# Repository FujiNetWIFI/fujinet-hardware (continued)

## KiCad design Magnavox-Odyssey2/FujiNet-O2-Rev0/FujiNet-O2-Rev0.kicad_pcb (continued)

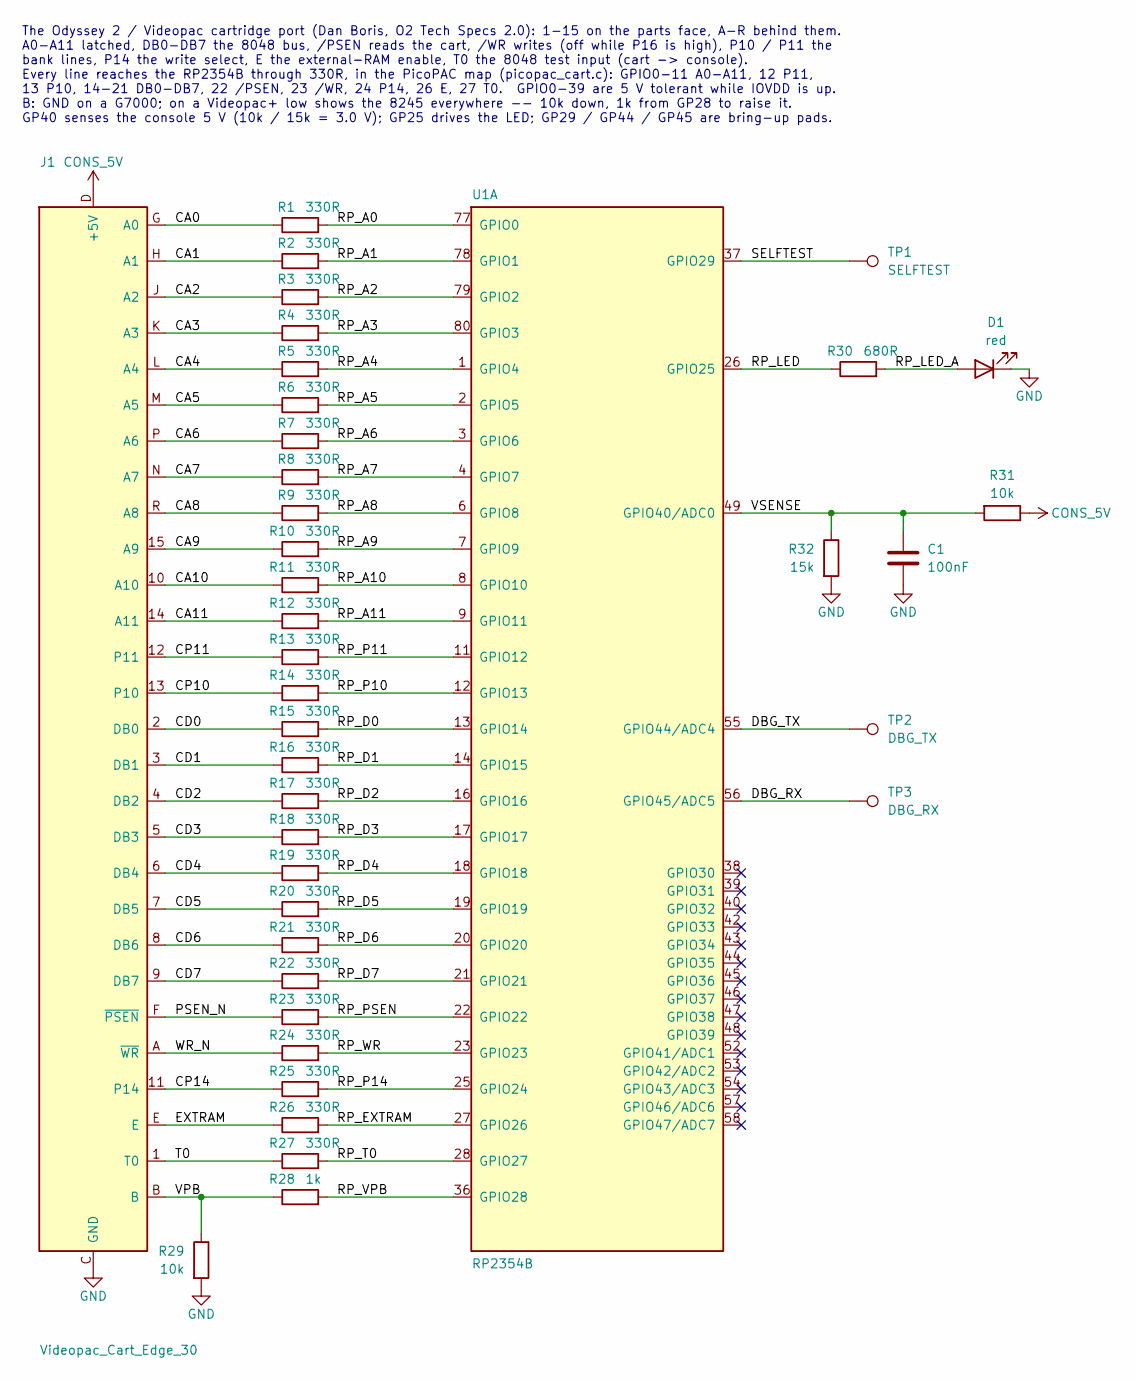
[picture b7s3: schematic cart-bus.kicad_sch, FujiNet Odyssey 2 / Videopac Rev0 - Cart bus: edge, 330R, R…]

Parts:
C1: 100nF; C_0603_1608Metric; MPN CC0603KRX7R9BB104; LCSC C14663
D1: red; LED_0603_1608Metric; MPN KT-0603R; LCSC C2286
J1: Videopac_Cart_Edge_30
R1, R2, R3, R4, R5, R6, R7, R8, R9, R10, R11, R12, R13, R14, R15, R16, R17, R18, R19, R20, R21, R22, R23, R24, R25, R26, R27: 330R; R_0603_1608Metric; MPN 0603WAF3300T5E; LCSC C23138
R28: 1k; R_0603_1608Metric; MPN 0603WAF1001T5E; LCSC C21190
R29, R31: 10k; R_0603_1608Metric; MPN 0603WAF1002T5E; LCSC C25804
R30: 680R; R_0603_1608Metric; MPN 0603WAF6800T5E; LCSC C23228
R32: 15k; R_0603_1608Metric; MPN 0603WAF1502T5E; LCSC C22809
TP1: SELFTEST; TestPoint_Pad_D1.5mm
TP2: DBG_TX; TestPoint_Pad_D1.5mm
TP3: DBG_RX; TestPoint_Pad_D1.5mm
U1: RP2354B; QFN-80-1EP_10x10mm_P0.4mm_EP3.4x3.4mm; MPN RP2354B; LCSC C39843328

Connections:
/cart-bus/CA0: J1.G (A0), R1.1
/cart-bus/CA1: J1.H (A1), R2.1
/cart-bus/CA2: J1.J (A2), R3.1
/cart-bus/CA3: J1.K (A3), R4.1
/cart-bus/CA4: J1.L (A4), R5.1
/cart-bus/CA5: J1.M (A5), R6.1
/cart-bus/CA6: J1.P (A6), R7.1
/cart-bus/CA7: J1.N (A7), R8.1
/cart-bus/CA8: J1.R (A8), R9.1
/cart-bus/CA9: J1.15 (A9), R10.1
/cart-bus/CA10: J1.10 (A10), R11.1
/cart-bus/CA11: J1.14 (A11), R12.1
/cart-bus/CD0: J1.2 (DB0), R15.1
/cart-bus/CD1: J1.3 (DB1), R16.1
/cart-bus/CD2: J1.4 (DB2), R17.1
/cart-bus/CD3: J1.5 (DB3), R18.1
/cart-bus/CD4: J1.6 (DB4), R19.1
/cart-bus/CD5: J1.7 (DB5), R20.1
/cart-bus/CD6: J1.8 (DB6), R21.1
/cart-bus/CD7: J1.9 (DB7), R22.1
/cart-bus/CP10: J1.13 (P10), R14.1
/cart-bus/CP11: J1.12 (P11), R13.1
/cart-bus/CP14: J1.11 (P14), R25.1
/cart-bus/DBG_RX: TP3.1, U1.56 (GPIO45/ADC5)
/cart-bus/DBG_TX: TP2.1, U1.55 (GPIO44/ADC4)
/cart-bus/EXTRAM: J1.E, R26.1
/cart-bus/PSEN_N: J1.F (~PSEN), R23.1
/cart-bus/RP_A0: R1.2, U1.77 (GPIO0)
/cart-bus/RP_A1: R2.2, U1.78 (GPIO1)
/cart-bus/RP_A2: R3.2, U1.79 (GPIO2)
/cart-bus/RP_A3: R4.2, U1.80 (GPIO3)
/cart-bus/RP_A4: R5.2, U1.1 (GPIO4)
/cart-bus/RP_A5: R6.2, U1.2 (GPIO5)
/cart-bus/RP_A6: R7.2, U1.3 (GPIO6)
/cart-bus/RP_A7: R8.2, U1.4 (GPIO7)
/cart-bus/RP_A8: R9.2, U1.6 (GPIO8)
/cart-bus/RP_A9: R10.2, U1.7 (GPIO9)
/cart-bus/RP_A10: R11.2, U1.8 (GPIO10)
/cart-bus/RP_A11: R12.2, U1.9 (GPIO11)
/cart-bus/RP_D0: R15.2, U1.13 (GPIO14)
/cart-bus/RP_D1: R16.2, U1.14 (GPIO15)
/cart-bus/RP_D2: R17.2, U1.16 (GPIO16)
/cart-bus/RP_D3: R18.2, U1.17 (GPIO17)
/cart-bus/RP_D4: R19.2, U1.18 (GPIO18)
/cart-bus/RP_D5: R20.2, U1.19 (GPIO19)
/cart-bus/RP_D6: R21.2, U1.20 (GPIO20)
/cart-bus/RP_D7: R22.2, U1.21 (GPIO21)
/cart-bus/RP_EXTRAM: R26.2, U1.27 (GPIO26)
/cart-bus/RP_LED: R30.1, U1.26 (GPIO25)
/cart-bus/RP_LED_A: D1.2 (A), R30.2
/cart-bus/RP_P10: R14.2, U1.12 (GPIO13)
/cart-bus/RP_P11: R13.2, U1.11 (GPIO12)
/cart-bus/RP_P14: R25.2, U1.25 (GPIO24)
/cart-bus/RP_PSEN: R23.2, U1.22 (GPIO22)
/cart-bus/RP_T0: R27.2, U1.28 (GPIO27)
/cart-bus/RP_VPB: R28.2, U1.36 (GPIO28)
/cart-bus/RP_WR: R24.2, U1.23 (GPIO23)
/cart-bus/SELFTEST: TP1.1, U1.37 (GPIO29)
/cart-bus/T0: J1.1 (T0), R27.1
/cart-bus/VPB: J1.B, R28.1, R29.1
/cart-bus/VSENSE: C1.1, R31.2, R32.1, U1.49 (GPIO40/ADC0)
/cart-bus/WR_N: J1.A (~WR), R24.1
CONS_5V: J1.D (+5V), R31.1; also elsewhere on the board
GND: C1.2, D1.1 (K), J1.C (GND), R29.2, R32.2; also elsewhere on the board

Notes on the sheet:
The Odyssey 2 / Videopac cartridge port (Dan Boris, O2 Tech Specs 2.0): 1-15 on the parts face, A-R behind them. A0-A11 latched, DB0-DB7 the 8048 bus, /PSEN reads the cart, /WR writes (off while P16 is high), P10 / P11 the bank lines, P14 the write select, E the external-RAM enable, T0 the 8048 tes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

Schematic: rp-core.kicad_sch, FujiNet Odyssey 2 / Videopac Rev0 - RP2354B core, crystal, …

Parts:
C2, C3, C4, C5, C6, C8, C9, C10, C12, C15, C16: 100nF; C_0603_1608Metric; MPN CC0603KRX7R9BB104; LCSC C14663
C7, C11, C17: 100nF; RPI_C0402; MPN CL05B104KO5NNNC; LCSC C1525
C13: 10uF; C_0603_1608Metric; MPN CL10A106KP8NNNC; LCSC C19702
C14, C18: 4.7uF; RPI_C0402_wide; MPN CL05A475MP5NRNC; LCSC C23733
C19: 4.7uF; RPI_C0402; MPN CL05A475MP5NRNC; LCSC C23733
C20, C21: 15pF; C_0603_1608Metric; MPN CL10C150JB8NNNC; LCSC C1644
D2: BAT54C; SOT-23; MPN BAT54C,215; LCSC C37704
L1: 3.3uH; RPI_L_AOTA-B201610S3R3; MPN AOTA-B201610S3R3-101-T; LCSC C42411119
R33: 33R; RPI_R0402; MPN 0402WGF330JTCE; LCSC C25105
R34, R36, R38, R39: 1k; R_0603_1608Metric; MPN 0603WAF1001T5E; LCSC C21190
R35, R37: 10k; R_0603_1608Metric; MPN 0603WAF1002T5E; LCSC C25804
R40, R41: 27R; RPI_R0402; MPN 0402WGF270JTCE; LCSC C25100
SW1: BOOTSEL; SW_SPST_TS-1187A; MPN TS-1187A-B-A-B; LCSC C318884
SW2: RESET; SW_SPST_TS-1187A; MPN TS-1187A-B-A-B; LCSC C318884
TP4: SWCLK; TestPoint_Pad_D1.5mm
TP5: SWDIO; TestPoint_Pad_D1.5mm
TP6: GND; TestPoint_Pad_D1.5mm
TP7: RUN; TestPoint_Pad_D1.5mm
TP8: DVDD; TestPoint_Pad_D1.5mm
U1: RP2354B; QFN-80-1EP_10x10mm_P0.4mm_EP3.4x3.4mm; MPN RP2354B; LCSC C39843328
Y1: 12MHz; Crystal_SMD_3225-4Pin_3.2x2.5mm; MPN ABM8-272-T3; LCSC C20625731

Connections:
+3V3_RP: C2.1, C3.1, C4.1, C5.1, C6.1, C7.1, C8.1, C9.1, C10.1, C11.1, C12.1, C13.1, C14.1, R33.1, R35.1, R37.1, U1.5 (IOVDD), U1.15 (IOVDD), U1.24 (IOVDD), U1.29 (IOVDD), U1.41 (IOVDD), U1.50 (IOVDD), U1.59 (ADC_AVDD), U1.60 (IOVDD), U1.64 (VREG_VIN), U1.68 (USB_OTP_VDD), U1.69 (QSPI_IOVDD), U1.76 (IOVDD); also elsewhere on the board
/BOOTSEL_CTL: R39.1; also elsewhere on the board
/RUN_CTL: R36.1; also elsewhere on the board
/S3_EN: D2.2; also elsewhere on the board
/USB_DM: R41.1; also elsewhere on the board
/USB_DP: R40.1; also elsewhere on the board
/rp-core/BOOTSEL_BTN: R38.2, SW1.1
/rp-core/QSPI_SS: R37.2, R38.1, R39.2, U1.75 (~QSPI_SS)
/rp-core/RP_LX: L1.2, U1.63 (VREG_LX)
/rp-core/RP_USB_DM: R41.2, U1.66 (USB_DM)
/rp-core/RP_USB_DP: R40.2, U1.67 (USB_DP)
/rp-core/RST_BTN: D2.3, SW2.1
/rp-core/RUN: D2.1, R35.2, R36.2, TP7.1, U1.35 (RUN)
/rp-core/SWCLK: TP4.1, U1.33 (SWCLK)
/rp-core/SWDIO: TP5.1, U1.34 (SWDIO)
/rp-core/VREG_AVDD: C19.1, R33.2, U1.61 (VREG_AVDD)
/rp-core/XIN: C20.1, U1.30 (XIN), Y1.1
/rp-core/XOUT: R34.1, U1.31 (XOUT)
/rp-core/XOUT_Y: C21.1, R34.2, Y1.3
DVDD: C15.1, C16.1, C17.1, C18.1, L1.1, TP8.1, U1.10 (DVDD), U1.32 (DVDD), U1.51 (DVDD), U1.65 (VREG_FB)
GND: C2.2, C3.2, C4.2, C5.2, C6.2, C7.2, C8.2, C9.2, C10.2, C11.2, C12.2, C13.2, C14.2, C15.2, C16.2, C17.2, C18.2, C19.2, C20.2, C21.2, SW1.2, SW2.2, TP6.1, U1.62 (VREG_PGND), U1.81 (GND), Y1.2 (G), Y1.4 (G); also elsewhere on the board

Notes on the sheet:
Supplies (RP2350 datasheet 6.3.7): IOVDD, QSPI_IOVDD, USB_OTP_VDD, ADC_AVDD and VREG_VIN on +3V3_RP, the AP2112K LDO that rises with +5V; the core regulator switches VREG_LX through 3.3 uH onto DVDD (VREG_FB senses it), its analog supply VREG_AVDD through 33R / 4.7 uF. One 100 nF at every supply pi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

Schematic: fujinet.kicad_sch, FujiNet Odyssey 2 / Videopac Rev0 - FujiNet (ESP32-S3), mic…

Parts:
C22: 22uF; C_0805_2012Metric; MPN CL21A226MAQNNNE; LCSC C45783
C23, C26: 100nF; C_0603_1608Metric; MPN CC0603KRX7R9BB104; LCSC C14663
C24: 1uF; C_0603_1608Metric; MPN CL10A105KB8NNNC; LCSC C15849
C25: 10uF; C_0603_1608Metric; MPN CL10A106KP8NNNC; LCSC C19702
D3: WS2812B-2020-V6; LED_WS2812B-2020_PLCC4_2.0x2.0mm; MPN WS2812B-2020-V6; LCSC C52917434
J2: microSD; TF-SMD_TF-015; MPN TF-015; LCSC C113206
R42, R43: 10k; R_0603_1608Metric; MPN 0603WAF1002T5E; LCSC C25804
R44: 330R; R_0603_1608Metric; MPN 0603WAF3300T5E; LCSC C23138
RN1: 4x10k; R_Array_Convex_4x0603; MPN 4D03WGJ0103T5E; LCSC C29718
SW3: S3_RST; SW_SPST_TS-1187A; MPN TS-1187A-B-A-B; LCSC C318884
SW4: S3_BOOT; SW_SPST_TS-1187A; MPN TS-1187A-B-A-B; LCSC C318884
U2: ESP32-S3-WROOM-1-N16R8; ESP32-S3-WROOM-1; MPN ESP32-S3-WROOM-1-N16R8; LCSC C2913202

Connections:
+3V3: C22.1, C23.1, C25.1, J2.4 (VDD), R42.1, R43.1, RN1.5 (R4.2), RN1.6 (R3.2), RN1.7 (R2.2), RN1.8 (R1.2), U2.2 (3V3); also elsewhere on the board
+5V: C26.1, D3.4 (VDD); also elsewhere on the board
/BOOTSEL_CTL: U2.5 (IO5); also elsewhere on the board
/RUN_CTL: U2.4 (IO4); also elsewhere on the board
/S3_EN: C24.1, R42.2, SW3.1, U2.3 (EN); also elsewhere on the board
/S3_IO0: SW4.1, U2.27 (IO0); also elsewhere on the board
/S3_RXD: U2.36 (RXD0); also elsewhere on the board
/S3_TXD: U2.37 (TXD0); also elsewhere on the board
/USB_DM: U2.13 (USB_D-); also elsewhere on the board
/USB_DP: U2.14 (USB_D+); also elsewhere on the board
/fujinet/LED_STRIP: R44.1, U2.25 (IO48)
/fujinet/SD_CD: J2.9 (CD), R43.2, U2.35 (IO42)
/fujinet/SD_CS: J2.2 (DAT3/CS), RN1.1 (R1.1), U2.34 (IO41)
/fujinet/SD_DAT1: J2.8 (DAT1), RN1.3 (R3.1)
/fujinet/SD_DAT2: J2.1 (DAT2), RN1.4 (R4.1)
/fujinet/SD_MISO: J2.7 (DAT0/DO), RN1.2 (R2.1), U2.33 (IO40)
/fujinet/SD_MOSI: J2.3 (CMD/DI), U2.31 (IO38)
/fujinet/SD_SCK: J2.5 (CLK), U2.32 (IO39)
/fujinet/WS_DIN: D3.3 (DIN), R44.2
GND: C22.2, C23.2, C24.2, C25.2, C26.2, D3.2 (VSS), J2.6 (VSS), J2.10 (SH), J2.11 (SH), J2.12 (SH), J2.13 (SH), SW3.2, SW4.2, U2.1 (GND), U2.40 (GND), U2.41 (GND); also elsewhere on the board

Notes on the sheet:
ESP32-S3-WROOM-1-N16R8: the FujiNet (fujiversal-o2.h pin map), on +3V3 (the buck). EN: 10k / 1 uF power-on delay. The S3_RST button, the cart RESET (rp-core, through the BAT54C) and the USB bridge's auto-program pair (usb sheet) all pull it low; S3_BOOT and the same pair pull IO0. IO4 / IO5 drive t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

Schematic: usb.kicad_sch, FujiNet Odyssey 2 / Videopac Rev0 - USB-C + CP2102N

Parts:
C27: 1uF; C_0603_1608Metric; MPN CL10A105KB8NNNC; LCSC C15849
C28, C29: 100nF; C_0603_1608Metric; MPN CC0603KRX7R9BB104; LCSC C14663
C30: 4.7uF; C_0603_1608Metric; MPN CL10A475KO8NNNC; LCSC C19666
J3: USB-C; USB_C_Receptacle_HRO_TYPE-C-31-M-12; MPN TYPE-C-31-M-12; LCSC C165948
R45, R46: 5.1k; R_0603_1608Metric; MPN 0603WAF5101T5E; LCSC C23186
R47: 22k; R_0603_1608Metric; MPN 0603WAF2202T5E; LCSC C31850
R48: 47k; R_0603_1608Metric; MPN 0603WAF4702T5E; LCSC C25819
R49: 1k; R_0603_1608Metric; MPN 0603WAF1001T5E; LCSC C21190
U3: USBLC6-2SC6; SOT-23-6; MPN USBLC6-2SC6; LCSC C7519
U4: CP2102N-A02-GQFN28; QFN-28-1EP_5x5mm_P0.5mm_EP3.35x3.35mm; MPN CP2102N-A02-GQFN28R; LCSC C964632
U5: UMH3N; SOT-363_SC-70-6; MPN UMH3N; LCSC C62892

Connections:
+3V3: C29.1, C30.1, R49.1, U4.6 (VDD), U4.7 (VREGIN); also elsewhere on the board
/S3_EN: U5.6 (C1); also elsewhere on the board
/S3_IO0: U5.3 (C2); also elsewhere on the board
/S3_RXD: U4.26 (TXD); also elsewhere on the board
/S3_TXD: U4.25 (RXD); also elsewhere on the board
/usb/CC1: J3.A5 (CC1), R45.1
/usb/CC2: J3.B5 (CC2), R46.1
/usb/CP_RST: R49.2, U4.9 (~RST)
/usb/UART_DTR: U4.28 (~DTR), U5.2 (B1), U5.4 (E2)
/usb/UART_RTS: U4.24 (~RTS), U5.1 (E1), U5.5 (B2)
/usb/UBRG_DM: J3.A7 (D-), J3.B7 (D-), U3.1 (I/O1), U3.6 (I/O1), U4.5 (D-)
/usb/UBRG_DP: J3.A6 (D+), J3.B6 (D+), U3.3 (I/O2), U3.4 (I/O2), U4.4 (D+)
/usb/VBUS_SNS: R47.2, R48.1, U4.8 (VBUS)
GND: C27.2, C28.2, C29.2, C30.2, J3.A1 (GND), J3.A12 (GND), J3.B1 (GND), J3.B12 (GND), J3.SH (SHIELD), R45.2, R46.2, R48.2, U3.2 (GND), U4.3 (GND), U4.23 (~CTS), U4.29 (GND); also elsewhere on the board
VBUS: C27.1, C28.1, J3.A4 (VBUS), J3.A9 (VBUS), J3.B4 (VBUS), J3.B9 (VBUS), R47.1, U3.5 (VBUS); also elsewhere on the board

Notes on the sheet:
esptool's auto-program pair, as on the ESP32-S3-DevKitC-1: DTR low with RTS high pulls EN low; RTS low with DTR high pulls IO0 low; both high or both low leave the S3 alone.

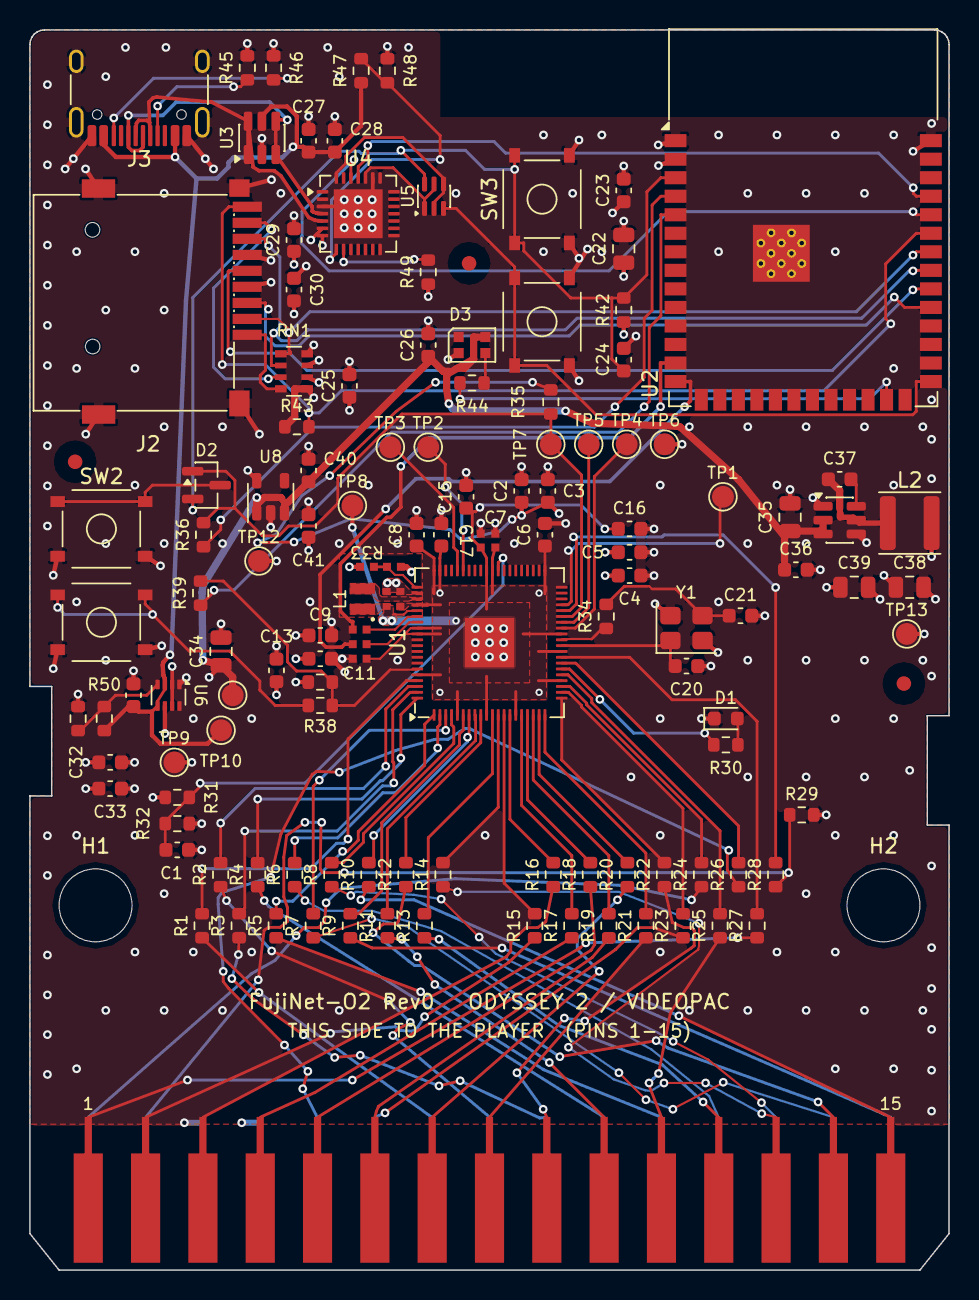
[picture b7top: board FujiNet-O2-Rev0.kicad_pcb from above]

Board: 4 copper layers, 63.0 x 85.0 mm, 132 parts (0 on the bottom side), 110 nets.

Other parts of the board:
FID1, FID2, FID3: Fiducial_1mm_Mask2mm
H1, H2: MountingHole_5mm_NPTH

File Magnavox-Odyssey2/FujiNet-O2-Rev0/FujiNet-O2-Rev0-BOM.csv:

Qty,References,Value,Footprint,MPN,Manufacturer,LCSC,Description,Notes
19,C1 C2 C3 C4 C5 C6 C8 C9 C10 C12 C15 C16 C23 C26 C28 C29 C33 C36 C37,100nF,C_0603_1608Metric,CC0603KRX7R9BB104,YAGEO,C14663,capacitor (several uses: see schematic),
3,C7 C11 C17,100nF,RPI_C0402,CL05B104KO5NNNC,Samsung Electro-Mechanics,C1525,capacitor (several uses: see schematic),
3,C13 C25 C32,10uF,C_0603_1608Metric,CL10A106KP8NNNC,Samsung Electro-Mechanics,C19702,capacitor (several uses: see schematic),
2,C14 C18,4.7uF,RPI_C0402_wide,CL05A475MP5NRNC,Samsung Electro-Mechanics,C23733,capacitor (several uses: see schematic),
1,C19,4.7uF,RPI_C0402,CL05A475MP5NRNC,Samsung Electro-Mechanics,C23733,VREG_AVDD filter,
2,C20 C21,15pF,C_0603_1608Metric,CL10C150JB8NNNC,Samsung Electro-Mechanics,C1644,crystal load,
5,C22 C34 C35 C38 C39,22uF,C_0805_2012Metric,CL21A226MAQNNNE,Samsung Electro-Mechanics,C45783,capacitor (several uses: see schematic),
5,C24 C27 C31 C40 C41,1uF,C_0603_1608Metric,CL10A105KB8NNNC,Samsung Electro-Mechanics,C15849,capacitor (several uses: see schematic),
1,C30,4.7uF,C_0603_1608Metric,CL10A475KO8NNNC,Samsung Electro-Mechanics,C19666,CP2102N VDD bulk,
1,D1,red,LED_0603_1608Metric,KT-0603R,Hubei KENTO Elec,C2286,RP activity LED (GP25),
1,D2,BAT54C,SOT-23,"BAT54C,215",Nexperia,C37704,"RESET steering, common cathode",
1,D3,WS2812B-2020-V6,LED_WS2812B-2020_PLCC4_2.0x2.0mm,WS2812B-2020-V6,Worldsemi,C52917434,status LED on +5V (datasheet VDD 3.7-5.3 V; VIH 2.7 V takes 3.3 V data),
1,J1,Videopac_Cart_Edge_30,Videopac_Cart_Edge_30,,,,"Odyssey 2 / Videopac cartridge edge, 2x15 gold fingers, 3.9286 mm pitch; 1-15 on the parts face, A-R behind them",not in BOM
1,J2,microSD,TF-SMD_TF-015,TF-015,SOFNG,C113206,"microSD push-push, SPI mode",
1,J3,USB-C,USB_C_Receptacle_HRO_TYPE-C-31-M-12,TYPE-C-31-M-12,Korean Hroparts Elec,C165948,power + S3 programming / console,
1,L1,3.3uH,RPI_L_AOTA-B201610S3R3,AOTA-B201610S3R3-101-T,Abracon,C42411119,RP2350 core SMPS inductor (polarity marked),
1,L2,6.8uH,L_Sunlord_SWPA4030S,SWPA4030S6R8MT,Sunlord,C62684,buck inductor,
28,R1 R2 R3 R4 R5 R6 R7 R8 R9 R10 R11 R12 R13 R14 R15 R16 R17 R18 R19 R20 R21 R22 R23 R24 R25 R26 R27 R44,330R,R_0603_1608Metric,0603WAF3300T5E,UNI-ROYAL,C23138,resistor (several uses: see schematic),
6,R28 R34 R36 R38 R39 R49,1k,R_0603_1608Metric,0603WAF1001T5E,UNI-ROYAL,C21190,resistor (several uses: see schematic),
7,R29 R31 R35 R37 R42 R43 R51,10k,R_0603_1608Metric,0603WAF1002T5E,UNI-ROYAL,C25804,resistor (several uses: see schematic),
1,R30,680R,R_0603_1608Metric,0603WAF6800T5E,UNI-ROYAL,C23228,LED series (~2 mA),
1,R32,15k,R_0603_1608Metric,0603WAF1502T5E,UNI-ROYAL,C22809,console 5V sense divider (0.6 x CONS_5V),
1,R33,33R,RPI_R0402,0402WGF330JTCE,UNI-ROYAL,C25105,VREG_AVDD filter,
2,R40 R41,27R,RPI_R0402,0402WGF270JTCE,UNI-ROYAL,C25100,USB series,
2,R45 R46,5.1k,R_0603_1608Metric,0603WAF5101T5E,UNI-ROYAL,C23186,UFP Rd,
1,R47,22k,R_0603_1608Metric,0603WAF2202T5E,UNI-ROYAL,C31850,VBUS sense divider,
1,R48,47k,R_0603_1608Metric,0603WAF4702T5E,UNI-ROYAL,C25819,VBUS sense divider,
1,R50,33k,R_0603_1608Metric,0603WAF3302T5E,UNI-ROYAL,C4216,mux priority threshold (VBUS > 4.3 V),
1,RN1,4x10k,R_Array_Convex_4x0603,4D03WGJ0103T5E,UNI-ROYAL,C29718,SD pull-ups,
1,SW1,BOOTSEL,SW_SPST_TS-1187A,TS-1187A-B-A-B,XKB Connection,C318884,RP2354B BOOTSEL (hold while pressing RESET),
1,SW2,RESET,SW_SPST_TS-1187A,TS-1187A-B-A-B,XKB Connection,C318884,cart RESET: RP RUN + S3 EN through the BAT54C,
1,SW3,S3_RST,SW_SPST_TS-1187A,TS-1187A-B-A-B,XKB Connection,C318884,ESP32-S3 EN,
1,SW4,S3_BOOT,SW_SPST_TS-1187A,TS-1187A-B-A-B,XKB Connection,C318884,ESP32-S3 BOOT (IO0),
1,TP1,SELFTEST,TestPoint_Pad_D1.5mm,,,,"test pad: GP29, a self-test trigger for bring-up",not in BOM
1,TP2,DBG_TX,TestPoint_Pad_D1.5mm,,,,"test pad: GP44, debug UART TX (3.3 V)",not in BOM
1,TP3,DBG_RX,TestPoint_Pad_D1.5mm,,,,"test pad: GP45, debug UART RX (3.3 V)",not in BOM
1,TP4,SWCLK,TestPoint_Pad_D1.5mm,,,,test pad,not in BOM
1,TP5,SWDIO,TestPoint_Pad_D1.5mm,,,,test pad,not in BOM
1,TP6,GND,TestPoint_Pad_D1.5mm,,,,test pad,not in BOM
1,TP7,RUN,TestPoint_Pad_D1.5mm,,,,test pad,not in BOM
1,TP8,DVDD,TestPoint_Pad_D1.5mm,,,,bring-up pad: RP core rail,not in BOM
1,TP9,CONS_5V,TestPoint_Pad_D1.5mm,,,,bring-up pad: console 5V (edge pin D),not in BOM
1,TP10,VBUS,TestPoint_Pad_D1.5mm,,,,bring-up pad: USB VBUS,not in BOM
1,TP11,+5V,TestPoint_Pad_D1.5mm,,,,bring-up pad: +5V (mux output),not in BOM
1,TP12,+3V3_RP,TestPoint_Pad_D1.5mm,,,,bring-up pad: +3V3_RP (RP LDO),not in BOM
1,TP13,+3V3,TestPoint_Pad_D1.5mm,,,,bring-up pad: +3V3 (buck: S3 side),not in BOM
1,U1,RP2354B,QFN-80-1EP_10x10mm_P0.4mm_EP3.4x3.4mm,RP2354B,Raspberry Pi,C39843328,RP2350B + 2MB flash in package; serves the Odyssey 2 cart bus,
1,U2,ESP32-S3-WROOM-1-N16R8,ESP32-S3-WROOM-1,ESP32-S3-WROOM-1-N16R8,Espressif,C2913202,FujiNet core (fujiversal-o2),
1,U3,USBLC6-2SC6,SOT-23-6,USBLC6-2SC6,STMicroelectronics,C7519,"USB ESD: D+, D-, VBUS",
1,U4,CP2102N-A02-GQFN28,QFN-28-1EP_5x5mm_P0.5mm_EP3.35x3.35mm,CP2102N-A02-GQFN28R,Silicon Labs,C964632,USB-UART for S3 flashing/console (self-powered),
1,U5,UMH3N,SOT-363_SC-70-6,UMH3N,Jiangsu Changjing (JSCJ),C62892,esptool auto-program (DevKitC-1 style),
1,U6,TPS2116,SOT-583-8,TPS2116DRLR,Texas Instruments,C3235557,"power mux: VBUS first, console 5V second",
1,U7,AP63203WU,TSOT-23-6,AP63203WU-7,Diodes Incorporated,C780769,"3.3V 2A buck (S3, SD, CP2102N)",
1,U8,AP2112K-3.3,SOT-23-5,AP2112K-3.3TRG1,Diodes Incorporated,C51118,"RP2354B 3.3V LDO (IOVDD, VREG_VIN, VREG_AVDD), 600mA, fast start",
1,Y1,12MHz,Crystal_SMD_3225-4Pin_3.2x2.5mm,ABM8-272-T3,Abracon,C20625731,RP2350 12 MHz crystal,

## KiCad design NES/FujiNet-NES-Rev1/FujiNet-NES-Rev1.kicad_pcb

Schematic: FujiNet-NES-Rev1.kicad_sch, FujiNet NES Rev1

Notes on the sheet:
72-pin cart edge, CIClone
RP-A: CPU bus, PRG, link, RP-B loader
RP-B: PPU bus, CHR and CIRAM
ESP32-S3, microSD, status LED
USB-C, CP2102N bridge
Power: 5V OR, 3.3V buck, two RP LDOs
FujiNet for the Nintendo Entertainment System - Rev1 (two RP2354Bs, no SRAM) RP-A (U1) sits on the CPU side of the 5V cart bus through its 5V-tolerant pads: CPU A0-A14, D0-D7, M2, R/W, /ROMSEL in, /IRQ out, PPU A12 in (MMC3 IRQ). It serves PRG from RAM (images up to 384K) or from its in-package fla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

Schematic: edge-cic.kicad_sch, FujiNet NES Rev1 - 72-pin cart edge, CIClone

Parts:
C41: 100nF; C_0603_1608Metric; MPN CC0603KRX7R9BB104; LCSC C14663; not fitted
J1: NES_Cart_Edge_72
R11: 2.2k; R_0603_1608Metric; MPN 0603WAF2201T5E; LCSC C4190
R12: 3.3k; R_0603_1608Metric; MPN 0603WAF3301T5E; LCSC C22978
TP7: M2; TestPoint_Pad_D1.5mm
TP13: CIC_RST; TestPoint_Pad_D1.5mm
U3: ATtiny13A-SSU; SOIC-8_3.9x4.9mm_P1.27mm; MPN ATTINY13A-SSUR; LCSC C40382; not fitted

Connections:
CA0: J1.13 (CPU A0); also elsewhere on the board
CA1: J1.12 (CPU A1); also elsewhere on the board
CA2: J1.11 (CPU A2); also elsewhere on the board
CA3: J1.10 (CPU A3); also elsewhere on the board
CA4: J1.9 (CPU A4); also elsewhere on the board
CA5: J1.8 (CPU A5); also elsewhere on the board
CA6: J1.7 (CPU A6); also elsewhere on the board
CA7: J1.6 (CPU A7); also elsewhere on the board
CA8: J1.5 (CPU A8); also elsewhere on the board
CA9: J1.4 (CPU A9); also elsewhere on the board
CA10: J1.3 (CPU A10); also elsewhere on the board
CA11: J1.2 (CPU A11); also elsewhere on the board
CA12: J1.39 (CPU A12); also elsewhere on the board
CA13: J1.40 (CPU A13); also elsewhere on the board
CA14: J1.41 (CPU A14); also elsewhere on the board
CD0: J1.49 (CPU D0); also elsewhere on the board
CD1: J1.48 (CPU D1); also elsewhere on the board
CD2: J1.47 (CPU D2); also elsewhere on the board
CD3: J1.46 (CPU D3); also elsewhere on the board
CD4: J1.45 (CPU D4); also elsewhere on the board
CD5: J1.44 (CPU D5); also elsewhere on the board
CD6: J1.43 (CPU D6); also elsewhere on the board
CD7: J1.42 (CPU D7); also elsewhere on the board
CIC_CLK: J1.71 (CIC CLK), U3.2 (PB3)
CIC_RESET_N: TP13.1, U3.1 (~RESET/PB5)
CIC_RST: J1.70 (CIC +RST), U3.7 (PB2)
CIC_TOMB: J1.35 (CIC toMB), U3.5 (PB0)
CIC_TOPAK: J1.34 (CIC toPak), U3.6 (PB1)
CIRAM_A10: J1.22 (CIRAM A10); also elsewhere on the board
CIRAM_CE_N: J1.57 (CIRAM ~CE); also elsewhere on the board
CONS_5V: C41.1, J1.36 (+5V), R11.1, U3.8 (VCC); also elsewhere on the board
GND: C41.2, J1.1 (GND), J1.72 (GND), R12.2, U3.4 (GND); also elsewhere on the board
IRQ_N: J1.15 (~IRQ); also elsewhere on the board
M2: J1.38 (M2), TP7.1; also elsewhere on the board
PA0: J1.29 (PPU A0); also elsewhere on the board
PA1: J1.28 (PPU A1); also elsewhere on the board
PA2: J1.27 (PPU A2); also elsewhere on the board
PA3: J1.26 (PPU A3); also elsewhere on the board
PA4: J1.25 (PPU A4); also elsewhere on the board
PA5: J1.24 (PPU A5); also elsewhere on the board
PA6: J1.23 (PPU A6); also elsewhere on the board
PA7: J1.59 (PPU A7); also elsewhere on the board
PA8: J1.60 (PPU A8); also elsewhere on the board
PA9: J1.61 (PPU A9); also elsewhere on the board
PA10: J1.63 (PPU A10); also elsewhere on the board
PA11: J1.62 (PPU A11); also elsewhere on the board
PA12: J1.64 (PPU A12); also elsewhere on the board
PA13: J1.65 (PPU A13); also elsewhere on the board
PD0: J1.30 (PPU D0); also elsewhere on the board
PD1: J1.31 (PPU D1); also elsewhere on the board
PD2: J1.32 (PPU D2); also elsewhere on the board
PD3: J1.33 (PPU D3); also elsewhere on the board
PD4: J1.69 (PPU D4); also elsewhere on the board
PD5: J1.68 (PPU D5); also elsewhere on the board
PD6: J1.67 (PPU D6); also elsewhere on the board
PD7: J1.66 (PPU D7); also elsewhere on the board
PPU_RD_N: J1.21 (PPU ~RD); also elsewhere on the board
PPU_WR_N: J1.56 (PPU ~WR); also elsewhere on the board
PWR_OK: R11.2, R12.1; also elsewhere on the board
ROMSEL_N: J1.50 (~ROMSEL); also elsewhere on the board
RW: J1.14 (CPU R/W); also elsewhere on the board

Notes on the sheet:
NES 72-pin edge drawn by function (finger numbers on the pins). Pin 1 is at the RIGHT seen from the label side with the fingers down (nesdev; NES-EWROM-01 geometry). EXP0-9, SYSTEM CLK and PPU /A13 are not used. The CIClone (ATtiny13A) is DNP until its firmware exists.

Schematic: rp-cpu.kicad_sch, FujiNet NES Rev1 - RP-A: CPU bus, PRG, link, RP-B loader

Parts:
C1, C2, C3, C4, C5, C6, C7, C8, C9, C10, C11, C14, C15, C16: 100nF; C_0603_1608Metric; MPN CC0603KRX7R9BB104; LCSC C14663
C12: 10uF; C_0603_1608Metric; MPN CL10A106KP8NNNC; LCSC C19702
C13, C17, C18: 4.7uF; C_0603_1608Metric; MPN CL10A475KO8NNNC; LCSC C19666
C19, C20: 15pF; C_0603_1608Metric; MPN CL10C150JB8NNNC; LCSC C1644
D1: BAT54C; SOT-23; MPN BAT54C,215; LCSC C37704
D2: red; LED_0603_1608Metric; MPN KT-0603R; LCSC C2286
L1: 3.3uH; RPI_L_AOTA-B201610S3R3; MPN AOTA-B201610S3R3-101-T; LCSC C42411119
R1: 33R; R_0603_1608Metric; MPN 0603WAF330JT5E; LCSC C23140
R2, R5, R6, R7: 1k; R_0603_1608Metric; MPN 0603WAF1001T5E; LCSC C21190
R3, R4: 10k; R_0603_1608Metric; MPN 0603WAF1002T5E; LCSC C25804
R8, R9: 27R; R_0603_1608Metric; MPN 0603WAF270JT5E; LCSC C25190
R10: 330R; R_0603_1608Metric; MPN 0603WAF3300T5E; LCSC C23138
SW1: RESET; SW_SPST_TL3342; MPN TL3342F160QG; LCSC C2886898
SW2: BOOTSEL; SW_SPST_TL3342; MPN TL3342F160QG; LCSC C2886898
TP1: SWCLK; TestPoint_Pad_D1.5mm
TP2: SWDIO; TestPoint_Pad_D1.5mm
TP3: GND; TestPoint_Pad_D1.5mm
TP4: RUN; TestPoint_Pad_D1.5mm
TP5: A_TX; TestPoint_Pad_D1.5mm
TP6: A_RX; TestPoint_Pad_D1.5mm
U1: RP2354B; QFN-80-1EP_10x10mm_P0.4mm_EP3.4x3.4mm; MPN RP2354B; LCSC C39843328
Y1: 12MHz; Crystal_SMD_3225-4Pin_3.2x2.5mm; MPN ABM8-272-T3; LCSC C20625731

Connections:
+3V3_RP: C1.1, C2.1, C3.1, C4.1, C5.1, C6.1, C7.1, C8.1, C9.1, C10.1, C11.1, C12.1, C13.1, R1.1, R3.1, R4.1, U1.5 (IOVDD), U1.15 (IOVDD), U1.24 (IOVDD), U1.29 (IOVDD), U1.41 (IOVDD), U1.50 (IOVDD), U1.59 (ADC_AVDD), U1.60 (IOVDD), U1.64 (VREG_VIN), U1.68 (USB_OTP_VDD), U1.69 (QSPI_IOVDD), U1.76 (IOVDD); also elsewhere on the board
BOOTSEL_BTN: R5.2, SW2.1
BOOTSEL_CTL: R7.1; also elsewhere on the board
CA0: U1.77 (GPIO0); also elsewhere on the board
CA1: U1.78 (GPIO1); also elsewhere on the board
CA2: U1.79 (GPIO2); also elsewhere on the board
CA3: U1.80 (GPIO3); also elsewhere on the board
CA4: U1.1 (GPIO4); also elsewhere on the board
CA5: U1.2 (GPIO5); also elsewhere on the board
CA6: U1.3 (GPIO6); also elsewhere on the board
CA7: U1.4 (GPIO7); also elsewhere on the board
CA8: U1.6 (GPIO8); also elsewhere on the board
CA9: U1.7 (GPIO9); also elsewhere on the board
CA10: U1.8 (GPIO10); also elsewhere on the board
CA11: U1.9 (GPIO11); also elsewhere on the board
CA12: U1.11 (GPIO12); also elsewhere on the board
CA13: U1.25 (GPIO24); also elsewhere on the board
CA14: U1.26 (GPIO25); also elsewhere on the board
CD0: U1.12 (GPIO13); also elsewhere on the board
CD1: U1.13 (GPIO14); also elsewhere on the board
CD2: U1.14 (GPIO15); also elsewhere on the board
CD3: U1.16 (GPIO16); also elsewhere on the board
CD4: U1.17 (GPIO17); also elsewhere on the board
CD5: U1.18 (GPIO18); also elsewhere on the board
CD6: U1.19 (GPIO19); also elsewhere on the board
CD7: U1.20 (GPIO20); also elsewhere on the board
DBG_A_RX: TP6.1, U1.37 (GPIO29)
DBG_A_TX: TP5.1, U1.36 (GPIO28)
DVDD: C14.1, C15.1, C16.1, C17.1, L1.1, U1.10 (DVDD), U1.32 (DVDD), U1.51 (DVDD), U1.65 (VREG_FB)
GND: C1.2, C2.2, C3.2, C4.2, C5.2, C6.2, C7.2, C8.2, C9.2, C10.2, C11.2, C12.2, C13.2, C14.2, C15.2, C16.2, C17.2, C18.2, C19.2, C20.2, D2.1 (K), SW1.2, SW2.2, TP3.1, U1.62 (VREG_PGND), U1.81 (GND), Y1.2 (G), Y1.4 (G); also elsewhere on the board
IRQ_N: U1.40 (GPIO32); also elsewhere on the board
LACK: U1.42 (GPIO33); also elsewhere on the board
LCLK: U1.53 (GPIO42/ADC2); also elsewhere on the board
LD0: U1.43 (GPIO34); also elsewhere on the board
LD1: U1.44 (GPIO35); also elsewhere on the board
LD2: U1.45 (GPIO36); also elsewhere on the board
LD3: U1.46 (GPIO37); also elsewhere on the board
LD4: U1.47 (GPIO38); also elsewhere on the board
LD5: U1.48 (GPIO39); also elsewhere on the board
LD6: U1.49 (GPIO40/ADC0); also elsewhere on the board
LD7: U1.52 (GPIO41/ADC1); also elsewhere on the board
LED: R10.1, U1.28 (GPIO27)
LED_A: D2.2 (A), R10.2
LFRM: U1.54 (GPIO43/ADC3); also elsewhere on the board
M2: U1.21 (GPIO21); also elsewhere on the board
PA12: U1.58 (GPIO47/ADC7); also elsewhere on the board
PWR_OK: U1.27 (GPIO26); also elsewhere on the board
QSPI_SS: R4.2, R5.1, R7.2, U1.75 (~QSPI_SS)
ROMSEL_N: U1.23 (GPIO23); also elsewhere on the board
RPB_RUN: U1.57 (GPIO46/ADC6); also elsewhere on the board
RPB_SWCLK: U1.55 (GPIO44/ADC4); also elsewhere on the board
RPB_SWDIO: U1.56 (GPIO45/ADC5); also elsewhere on the board
RP_LX: L1.2, U1.63 (VREG_LX)
RP_USB_DM: R9.2, U1.66 (USB_DM)
RP_USB_DP: R8.2, U1.67 (USB_DP)
RST_BTN: D1.3, SW1.1
RUN: D1.1, R3.2, R6.2, TP4.1, U1.35 (RUN)
RUN_CTL: R6.1; also elsewhere on the board
RW: U1.22 (GPIO22); also elsewhere on the board
S3_EN: D1.2; also elsewhere on the board
SWCLK: TP1.1, U1.33 (SWCLK)
SWDIO: TP2.1, U1.34 (SWDIO)
USB_DM: R9.1; also elsewhere on the board
USB_DP: R8.1; also elsewhere on the board
VREG_AVDD: C18.1, R1.2, U1.61 (VREG_AVDD)
XIN: C19.1, U1.30 (XIN), Y1.1
XOUT: R2.1, U1.31 (XOUT)
XOUT_Y: C20.1, R2.2, Y1.3

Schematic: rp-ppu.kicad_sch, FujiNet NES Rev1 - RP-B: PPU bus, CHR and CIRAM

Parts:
C21, C22, C23, C24, C25, C26, C27, C28, C29, C30, C31, C34, C35, C36: 100nF; C_0603_1608Metric; MPN CC0603KRX7R9BB104; LCSC C14663
C32: 10uF; C_0603_1608Metric; MPN CL10A106KP8NNNC; LCSC C19702
C33, C37, C38: 4.7uF; C_0603_1608Metric; MPN CL10A475KO8NNNC; LCSC C19666
C39, C40: 15pF; C_0603_1608Metric; MPN CL10C150JB8NNNC; LCSC C1644
L2: 3.3uH; RPI_L_AOTA-B201610S3R3; MPN AOTA-B201610S3R3-101-T; LCSC C42411119
R13: 33R; R_0603_1608Metric; MPN 0603WAF330JT5E; LCSC C23140
R14: 1k; R_0603_1608Metric; MPN 0603WAF1001T5E; LCSC C21190
R15, R16: 10k; R_0603_1608Metric; MPN 0603WAF1002T5E; LCSC C25804
TP8: B_SWCLK; TestPoint_Pad_D1.5mm
TP9: B_SWDIO; TestPoint_Pad_D1.5mm
TP10: B_RUN; TestPoint_Pad_D1.5mm
TP11: B_TX; TestPoint_Pad_D1.5mm
TP12: B_RX; TestPoint_Pad_D1.5mm
U2: RP2354B; QFN-80-1EP_10x10mm_P0.4mm_EP3.4x3.4mm; MPN RP2354B; LCSC C39843328
Y2: 12MHz; Crystal_SMD_3225-4Pin_3.2x2.5mm; MPN ABM8-272-T3; LCSC C20625731

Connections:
+3V3_RPB: C21.1, C22.1, C23.1, C24.1, C25.1, C26.1, C27.1, C28.1, C29.1, C30.1, C31.1, C32.1, C33.1, R13.1, R15.1, R16.1, U2.5 (IOVDD), U2.15 (IOVDD), U2.24 (IOVDD), U2.29 (IOVDD), U2.41 (IOVDD), U2.50 (IOVDD), U2.59 (ADC_AVDD), U2.60 (IOVDD), U2.64 (VREG_VIN), U2.68 (USB_OTP_VDD), U2.69 (QSPI_IOVDD), U2.76 (IOVDD); also elsewhere on the board
CIRAM_A10: U2.26 (GPIO25); also elsewhere on the board
CIRAM_CE_N: U2.27 (GPIO26); also elsewhere on the board
DBG_B_RX: TP12.1, U2.37 (GPIO29)
DBG_B_TX: TP11.1, U2.36 (GPIO28)
DVDD_B: C34.1, C35.1, C36.1, C37.1, L2.1, U2.10 (DVDD), U2.32 (DVDD), U2.51 (DVDD), U2.65 (VREG_FB)
GND: C21.2, C22.2, C23.2, C24.2, C25.2, C26.2, C27.2, C28.2, C29.2, C30.2, C31.2, C32.2, C33.2, C34.2, C35.2, C36.2, C37.2, C38.2, C39.2, C40.2, U2.62 (VREG_PGND), U2.81 (GND), Y2.2 (G), Y2.4 (G); also elsewhere on the board
LACK: U2.54 (GPIO43/ADC3); also elsewhere on the board
LCLK: U2.43 (GPIO34); also elsewhere on the board
LD0: U2.53 (GPIO42/ADC2); also elsewhere on the board
LD1: U2.52 (GPIO41/ADC1); also elsewhere on the board
LD2: U2.49 (GPIO40/ADC0); also elsewhere on the board
LD3: U2.48 (GPIO39); also elsewhere on the board
LD4: U2.47 (GPIO38); also elsewhere on the board
LD5: U2.46 (GPIO37); also elsewhere on the board
LD6: U2.45 (GPIO36); also elsewhere on the board
LD7: U2.44 (GPIO35); also elsewhere on the board
LFRM: U2.42 (GPIO33); also elsewhere on the board
PA0: U2.77 (GPIO0); also elsewhere on the board
PA1: U2.78 (GPIO1); also elsewhere on the board
PA2: U2.79 (GPIO2); also elsewhere on the board
PA3: U2.80 (GPIO3); also elsewhere on the board
PA4: U2.1 (GPIO4); also elsewhere on the board
PA5: U2.2 (GPIO5); also elsewhere on the board
PA6: U2.3 (GPIO6); also elsewhere on the board
PA7: U2.4 (GPIO7); also elsewhere on the board
PA8: U2.6 (GPIO8); also elsewhere on the board
PA9: U2.7 (GPIO9); also elsewhere on the board
PA10: U2.8 (GPIO10); also elsewhere on the board
PA11: U2.9 (GPIO11); also elsewhere on the board
PA12: U2.11 (GPIO12); also elsewhere on the board
PA13: U2.12 (GPIO13); also elsewhere on the board
PD0: U2.13 (GPIO14); also elsewhere on the board
PD1: U2.14 (GPIO15); also elsewhere on the board
PD2: U2.16 (GPIO16); also elsewhere on the board
PD3: U2.17 (GPIO17); also elsewhere on the board
PD4: U2.18 (GPIO18); also elsewhere on the board
PD5: U2.19 (GPIO19); also elsewhere on the board
PD6: U2.20 (GPIO20); also elsewhere on the board
PD7: U2.21 (GPIO21); also elsewhere on the board
PPU_RD_N: U2.22 (GPIO22); also elsewhere on the board
PPU_WR_N: U2.23 (GPIO23); also elsewhere on the board
PWR_OK: U2.25 (GPIO24), U2.55 (GPIO44/ADC4); also elsewhere on the board
QSPI_SS_B: R16.2, U2.75 (~QSPI_SS)
RPB_LX: L2.2, U2.63 (VREG_LX)
RPB_RUN: R15.2, TP10.1, U2.35 (RUN); also elsewhere on the board
RPB_SWCLK: TP8.1, U2.33 (SWCLK); also elsewhere on the board
RPB_SWDIO: TP9.1, U2.34 (SWDIO); also elsewhere on the board
VREG_AVDD_B: C38.1, R13.2, U2.61 (VREG_AVDD)
XIN_B: C39.1, U2.30 (XIN), Y2.1
XOUT_B: R14.1, U2.31 (XOUT)
XOUT_Y_B: C40.1, R14.2, Y2.3

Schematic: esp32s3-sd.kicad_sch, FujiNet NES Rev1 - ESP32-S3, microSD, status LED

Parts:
C42: 22uF; C_0805_2012Metric; MPN CL21A226MAQNNNE; LCSC C45783
C43, C46: 100nF; C_0603_1608Metric; MPN CC0603KRX7R9BB104; LCSC C14663
C44: 1uF; C_0603_1608Metric; MPN CL10A105KB8NNNC; LCSC C15849
C45: 10uF; C_0603_1608Metric; MPN CL10A106KP8NNNC; LCSC C19702
D3: WS2812B-2020-V6; LED_WS2812B-2020_PLCC4_2.0x2.0mm; MPN WS2812B-2020-V6; LCSC C52917434
J2: microSD; TF-SMD_TF-015; MPN TF-015; LCSC C113206
R17, R18: 10k; R_0603_1608Metric; MPN 0603WAF1002T5E; LCSC C25804
R19: 330R; R_0603_1608Metric; MPN 0603WAF3300T5E; LCSC C23138
RN1: 4x10k; R_Array_Convex_4x0603; MPN 4D03WGJ0103T5E; LCSC C29718
SW3: S3_RST; SW_SPST_TL3342; MPN TL3342F160QG; LCSC C2886898
SW4: S3_BOOT; SW_SPST_TL3342; MPN TL3342F160QG; LCSC C2886898
U4: ESP32-S3-WROOM-1-N16R8; ESP32-S3-WROOM-1; MPN ESP32-S3-WROOM-1-N16R8; LCSC C2913202

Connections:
+3V3: C42.1, C43.1, C45.1, J2.4 (VDD), R17.1, R18.1, RN1.5 (R4.2), RN1.6 (R3.2), RN1.7 (R2.2), RN1.8 (R1.2), U4.2 (3V3); also elsewhere on the board
+5V: C46.1, D3.4 (VDD); also elsewhere on the board
BOOTSEL_CTL: U4.5 (IO5); also elsewhere on the board
GND: C42.2, C43.2, C44.2, C45.2, C46.2, D3.2 (VSS), J2.6 (VSS), J2.10 (SH), J2.11 (SH), J2.12 (SH), J2.13 (SH), SW3.2, SW4.2, U4.1 (GND), U4.40 (GND), U4.41 (GND); also elsewhere on the board
LED_STRIP: R19.1, U4.25 (IO48)
RUN_CTL: U4.4 (IO4); also elsewhere on the board
S3_EN: C44.1, R17.2, SW3.1, U4.3 (EN); also elsewhere on the board
S3_IO0: SW4.1, U4.27 (IO0); also elsewhere on the board
S3_RXD: U4.36 (RXD0); also elsewhere on the board
S3_TXD: U4.37 (TXD0); also elsewhere on the board
SD_CD: J2.9 (CD), R18.2, U4.35 (IO42)
SD_CS: J2.2 (DAT3/CS), RN1.1 (R1.1), U4.34 (IO41)
SD_DAT1: J2.8 (DAT1), RN1.3 (R3.1)
SD_DAT2: J2.1 (DAT2), RN1.4 (R4.1)
SD_MISO: J2.7 (DAT0/DO), RN1.2 (R2.1), U4.33 (IO40)
SD_MOSI: J2.3 (CMD/DI), U4.31 (IO38)
SD_SCK: J2.5 (CLK), U4.32 (IO39)
USB_DM: U4.13 (USB_D-); also elsewhere on the board
USB_DP: U4.14 (USB_D+); also elsewhere on the board
WS_DIN: D3.3 (DIN), R19.2

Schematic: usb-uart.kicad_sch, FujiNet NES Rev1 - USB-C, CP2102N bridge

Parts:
C47: 1uF; C_0603_1608Metric; MPN CL10A105KB8NNNC; LCSC C15849
C48, C49: 100nF; C_0603_1608Metric; MPN CC0603KRX7R9BB104; LCSC C14663
C50: 4.7uF; C_0603_1608Metric; MPN CL10A475KO8NNNC; LCSC C19666
D4, D5, D6: ESD5Z5.0T1G; D_SOD-523; MPN ESD5Z5.0T1G; LCSC C82044
J3: USB-C; USB_C_Receptacle_HRO_TYPE-C-31-M-12; MPN TYPE-C-31-M-12; LCSC C165948
R20, R21: 5.1k; R_0603_1608Metric; MPN 0603WAF5101T5E; LCSC C23186
R22: 22k; R_0603_1608Metric; MPN 0603WAF2202T5E; LCSC C31850
R23: 47k; R_0603_1608Metric; MPN 0603WAF4702T5E; LCSC C25819
R24: 10k; R_0603_1608Metric; MPN 0603WAF1002T5E; LCSC C25804
U5: CP2102N-A02-GQFN28; QFN-28-1EP_5x5mm_P0.5mm_EP3.35x3.35mm; MPN CP2102N-A02-GQFN28R; LCSC C964632
U6: UMH3N; SOT-363_SC-70-6; MPN UMH3N; LCSC C62892

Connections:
+3V3: C49.1, C50.1, R24.1, U5.6 (VDD), U5.7 (VREGIN); also elsewhere on the board
CC1: J3.A5 (CC1), R20.1
CC2: J3.B5 (CC2), R21.1
CP_RST: R24.2, U5.9 (~RST)
GND: C47.2, C48.2, C49.2, C50.2, D4.2 (A), D5.2 (A), D6.2 (A), J3.A1 (GND), J3.A12 (GND), J3.B1 (GND), J3.B12 (GND), J3.SH (SHIELD), R20.2, R21.2, R23.2, U5.3 (GND), U5.23 (~CTS), U5.29 (GND); also elsewhere on the board
S3_EN: U6.6 (C1); also elsewhere on the board
S3_IO0: U6.3 (C2); also elsewhere on the board
S3_RXD: U5.26 (TXD); also elsewhere on the board
S3_TXD: U5.25 (RXD); also elsewhere on the board
UART_DTR: U5.28 (~DTR), U6.2 (B1), U6.4 (E2)
UART_RTS: U5.24 (~RTS), U6.1 (E1), U6.5 (B2)
UBRG_DM: D5.1 (K), J3.A7 (D-), J3.B7 (D-), U5.5 (D-)
UBRG_DP: D4.1 (K), J3.A6 (D+), J3.B6 (D+), U5.4 (D+)
VBUS: C47.1, C48.1, D6.1 (K), J3.A4 (VBUS), J3.A9 (VBUS), J3.B4 (VBUS), J3.B9 (VBUS), R22.1; also elsewhere on the board
VBUS_SNS: R22.2, R23.1, U5.8 (VBUS)
